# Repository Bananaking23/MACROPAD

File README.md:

# MACROPAD
This is my take on the HackPad Macropad from HackClub, It is my first time making a custom pcb or macropad.

This Macropad has 9 buttons, 2 mini leds, and a capacitive touch button

# Features
- 3d printed case
- 2 leds to show status/ layer
- customisable layers using kmk
- capacaitive touch button to swap layers.

# Photos

## Final product example when finished:

## Screenshot of Schematic

## Screenshot of PCB:

## Screenshot of case:

it is put together using 4 screws and heat inserts.
### Dimensions
80.46mm(W)x14.5mm(H)x104.44mm(L)

## BOM(prices are estimate):

# After Completion 
## Features
- 3x3 Macropad
- 3d printed case
- customisable layer and switches through a custom app
- 2 customisable leds
- 1 capacitive touch button for changing layers

## Photos
### The Macropad

### The Software

IMO great software, easy to use too
#### Main Menu

#### Sections

The flasher is built into the software, so no need for external softwares

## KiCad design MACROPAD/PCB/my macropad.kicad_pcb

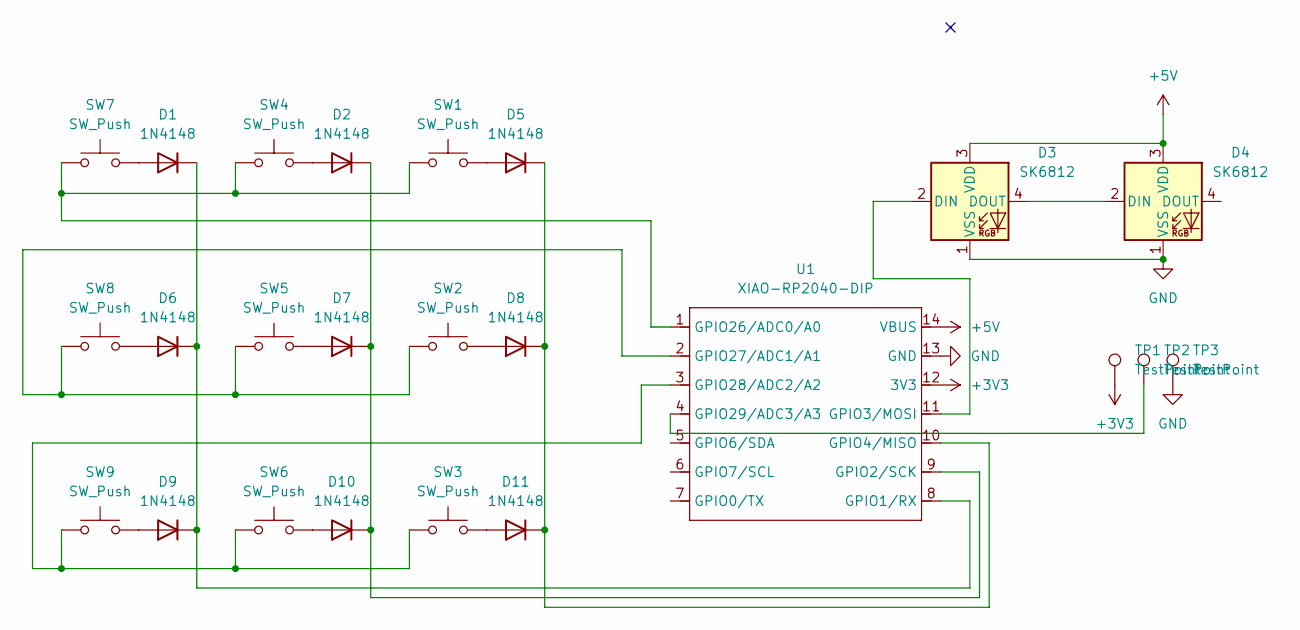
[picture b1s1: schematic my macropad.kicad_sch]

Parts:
D1, D2, D5, D6, D7, D8, D9, D10, D11: 1N4148; D_DO-35_SOD27_P7.62mm_Horizontal
D3, D4: SK6812; LED_SK6812MINI_PLCC4_3.5x3.5mm_P1.75mm
SW1, SW2, SW3, SW4, SW5, SW6, SW7, SW8, SW9: SW_Push; SW_Cherry_MX_1.00u_PCB
TP1, TP2, TP3: TestPoint; SolderWirePad_1x01_SMD_2x4mm
U1: XIAO-RP2040-DIP

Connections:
+3V3: TP1.1, U1.12 (3V3)
+5V: D3.3 (VDD), D4.3 (VDD), U1.14 (VBUS)
GND: D3.1 (VSS), D4.1 (VSS), TP3.1, U1.13 (GND)
unnamed: D1.2 (A), SW7.2
unnamed: D1.1 (K), D6.1 (K), D9.1 (K), U1.8 (GPIO1/RX)
unnamed: D2.2 (A), SW4.2
unnamed: D3.2 (DIN), U1.11 (GPIO3/MOSI)
unnamed: D3.4 (DOUT), D4.2 (DIN)
unnamed: D5.2 (A), SW1.2
unnamed: D6.2 (A), SW8.2
unnamed: D7.2 (A), SW5.2
unnamed: D8.2 (A), SW2.2
unnamed: D9.2 (A), SW9.2
unnamed: D10.2 (A), SW6.2
unnamed: D2.1 (K), D7.1 (K), D10.1 (K), U1.9 (GPIO2/SCK)
unnamed: D11.2 (A), SW3.2
unnamed: D5.1 (K), D8.1 (K), D11.1 (K), U1.10 (GPIO4/MISO)
unnamed: SW1.1, SW4.1, SW7.1, U1.1 (GPIO26/ADC0/A0)
unnamed: SW2.1, SW5.1, SW8.1, U1.2 (GPIO27/ADC1/A1)
unnamed: SW3.1, SW6.1, SW9.1, U1.3 (GPIO28/ADC2/A2)
unnamed: TP2.1, U1.4 (GPIO29/ADC3/A3)

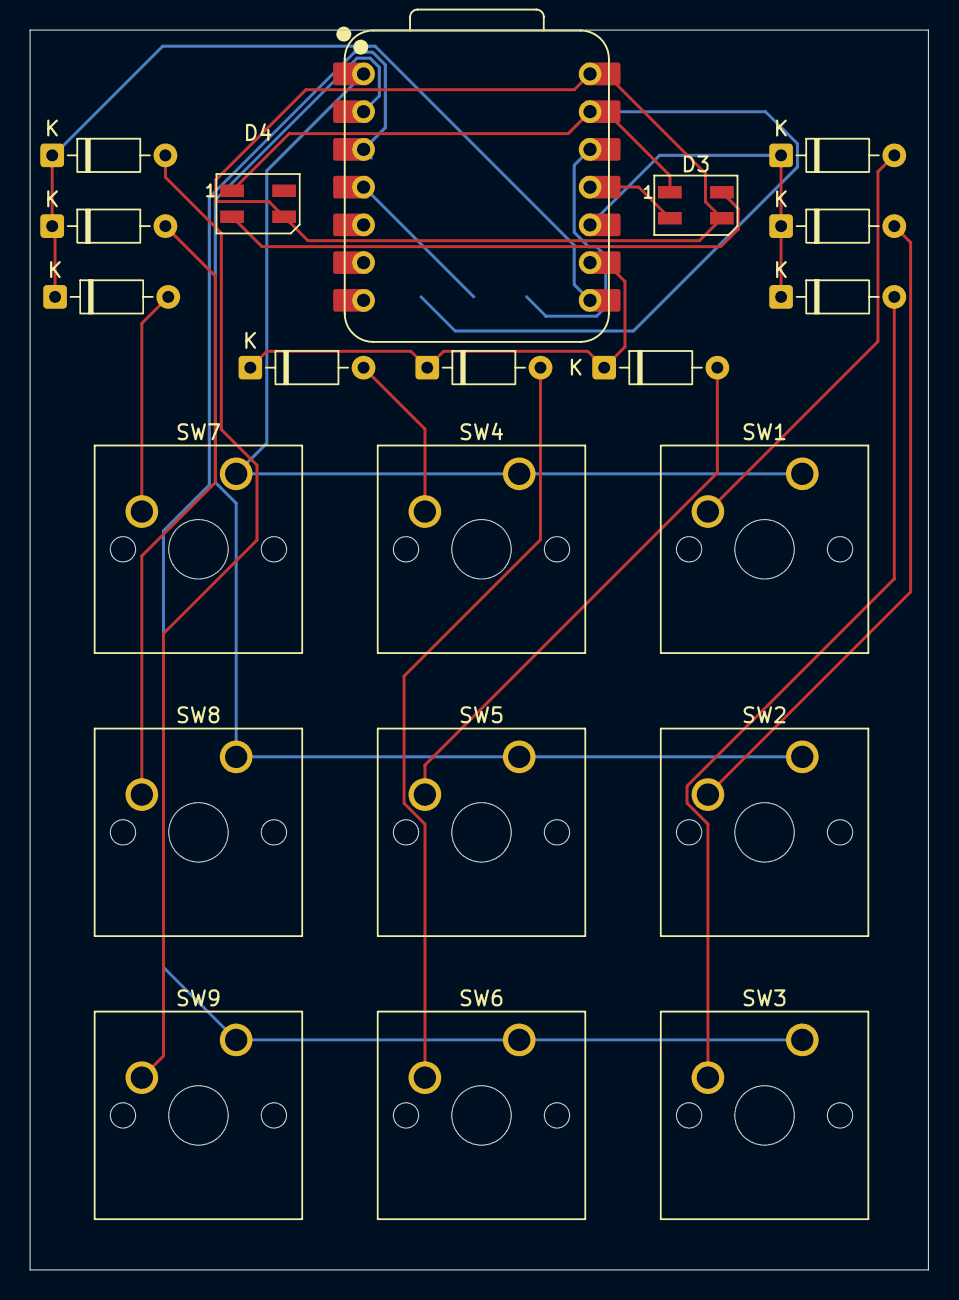
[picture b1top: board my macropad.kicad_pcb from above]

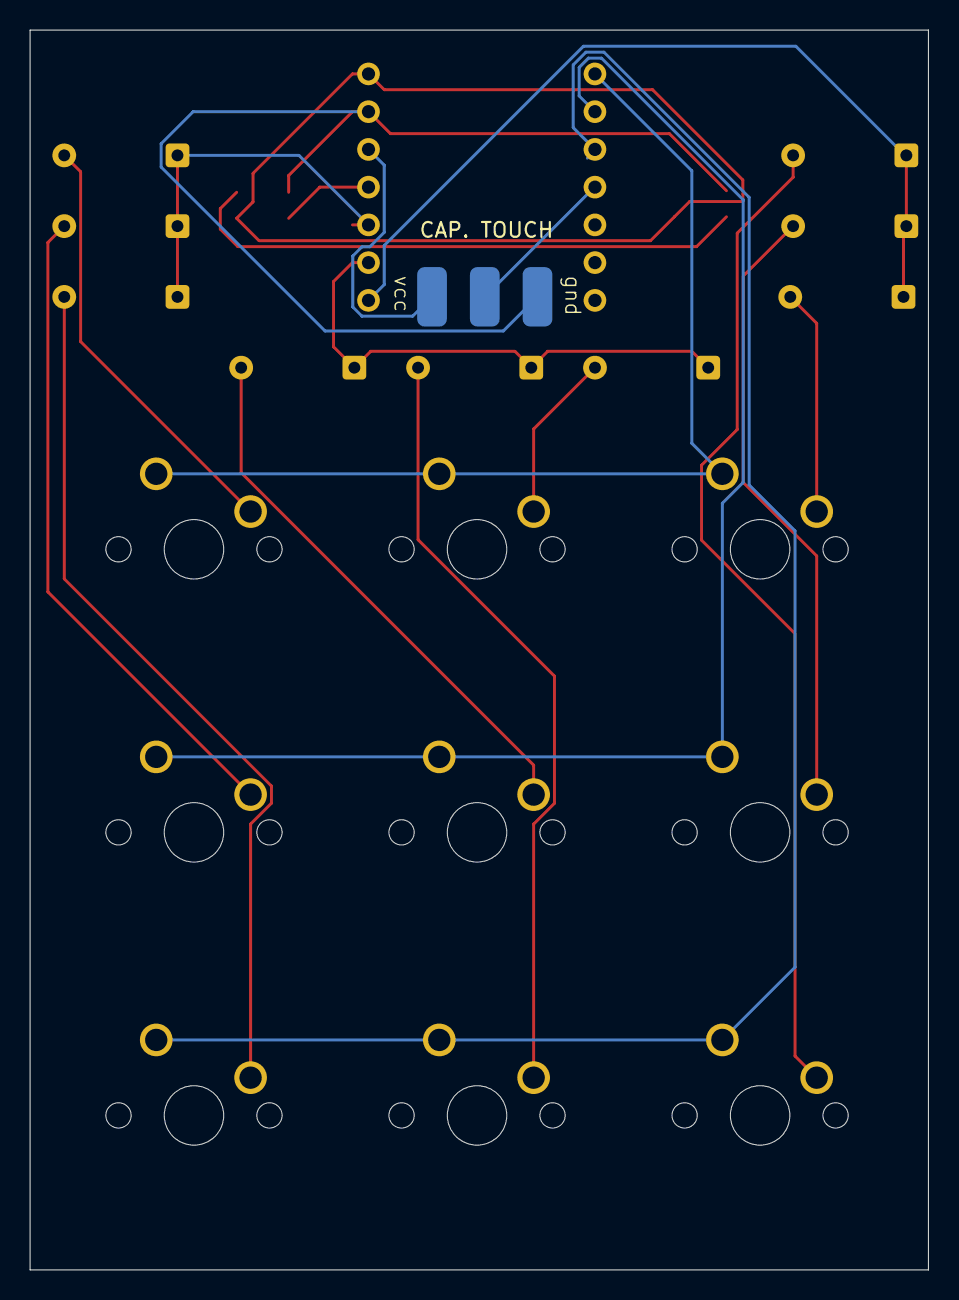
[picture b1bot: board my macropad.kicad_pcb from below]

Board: 2 copper layers, 60.5 x 83.4 mm, 24 parts (3 on the bottom side), 21 nets.

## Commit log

2026-01-20 Add image to README for MACROPAD
2026-01-20 Enhance README with photos and pin definitions
    Added sections for photos and pin definitions to README.
2026-03-04 Update image alt text and section headings in README
2026-03-04 Change 'Play Menu' to 'Main Menu'
    Updated section headers in the README file.
